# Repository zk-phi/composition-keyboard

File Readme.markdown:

# Composition 0.1

Choc V2 スイッチを採用した一体型・直交配列 40% キーボードです。 Choc V2 由来の薄さと、強めにつけた丸みが特徴的な可愛めのデザインになっています。透明アクリルで作るとよく光ります。

また自分のキーボードではお馴染みになっている、内部の空洞を廃した積層ケースを採用しており、アクリルにしてはしっかりした打鍵感を実現しています。今回はスイッチの性質上プレートレスの設計になっており、 PCB とケースの間の空間がまったくないので、他の作品よりもやや硬めの打鍵感になります。 PCB とケースの間にゴムワッシャなどの緩衝材を入れても問題なく使えることを確認しているので、柔らかい打鍵感が好きな場合はなんちゃってガスケットマウント化して使うのもアリかもしれないです。

# 注意

Choc V2 は「MX 互換スイッチと同じキーキャップをはめることができるが、 MX 互換スイッチよりかなり薄い」という特殊なスイッチです。

キーキャップの選択肢問題をクリアしつつキーボードを薄型化できる優秀なスイッチですが、いくつか注意点もあります。

## 全ての MX 互換キーキャップが使えるわけではない

キーキャップ側は Choc V2 を想定して設計されているわけではないので、一部噛み合わないものもあるようです。把握している範囲では、 GMK などの Cherry プロファイル、 RAMA の GRID キーキャップなどは難ありでした。

## トッププレートなし設計

トッププレートがキーキャップに干渉してしまうため、トッププレートなしの設計になっています。そのため、スイッチを半田付けする際の位置決めにコツが要ります。また基板を直接アクリル板に固定する都合、基板の歪みがキーボード全体の歪みに繋がりやすいです。

対策についても組み立てガイドの中で解説していますのでご確認ください。

## Pro Micro のレイアウトについて

このキーボードは Pro Micro を採用しつつ Choc V2 の薄さも活かすため、 Pro Micro 部分をケースの外に追い出す設計になっています（写真３枚目参照）。

無茶な使い方 (Pro Micro が外れかけた状態で金属製の机に置く、とか…) をするとショートの危険があるため、心配な方は

- あえてコンスルーを使わずに Pro Micro を直接半田付けして、ゆるまないようにする
- 絶縁テープ等をあらかじめ貼っておく

など各自工夫してお使いください（自分はあまり気にせず使っています）。

# 必要なもの

キット
- 基板
- トップフレーム 2mm x 1, 3mm x 1
- ミドルプレート (2mm)
- ボトムプレート上 (3mm)
- ボトムプレート下 (3mm)

おまけ
- ボトムプレート下 (2mm)

汎用部品
- キースイッチ, キーキャップ, ダイオード 1N4148w x41
- LED SK6812mini x56
- 2pin タクトスイッチ x1
- Pro Micro + ピンヘッダまたはコンスルー
- M2 ねじ 14mm x13, 6mm x7
- M2 ナット x20
- ゴムクッション x4 以上

カスタマイズに使えそうな部品 (任意)
- ゴムワッシャ

# 予備部品について

「ボトムプレート下」に 2mm のものを使ってさらに 1mm 薄くすることもできます。

打面を 1mm 下げ打鍵感を変化させられるほか、デザイン的にもミドルプレートを中心に上下対称となって綺麗に見えます。

ただし、 Pro Micro に取り付けたコンスルー（ピンヘッダ）の足がケースをはみ出してしまうため、足をカットするなどして、机に触れてしまうことがないようひと工夫する必要があります。

組み立てガイドではより無難な 3mm をデフォルトとしますが、興味のある方は自己責任にてチャンレンジしてみてください。

# 組み立て
## ProMicro の準備
### ProMicro にファームウェアを書き込んでおく

ProMicro にあらかじめファームウェアを書き込んでおきます。

https://github.com/zk-phi/keyboard-buildguide-common/blob/master/firmware.markdown

[こちら](https://github.com/zk-phi/qmk_firmware) に私の使っているキーマップがアップロードされています。

```terminal
make composition:phi:avrdude
```

### ProMicro にコンスルーを実装しておく

ProMicro を基板に連結するためのコンスルーを実装します。

https://github.com/zk-phi/keyboard-buildguide-common/blob/master/conthrough.markdown

このキーボードでは ProMicro を「部品面が内側になるように」使用します。

## 基板の歪みを矯正

このキーボードは基板を直接ケースにねじ止めして一体化させる設計になっているので、基板の歪みが激しいと、最終的に完成するキーボード全体も歪んでしまうことがあります。

そこで、半田付けを始める前に、基板を損傷しない程度に軽く歪みを矯正しておくことをおすすめします。

## 基板に各パーツを実装

### ダイオードを実装

ダイオードを実装します。

https://github.com/zk-phi/keyboard-buildguide-common/blob/master/diode.markdown

表面実装部品は、ガイドの印から大きくはみ出して取り付けてしまうと「ボトムプレート上」と干渉してケースが組めなくなってしまいますので、なるべく丁寧に位置を合わせてください。

### LED を実装 (オプション)

LED を実装します。

https://github.com/zk-phi/keyboard-buildguide-common/blob/master/neopixel.markdown

LED の実装順は Pro Micro 側上段のバックライト (背面実装・赤) からスタートして Z 字に降りていき、下段まで行ったらアンダーグロー (表面実装・青) で折り返すように進みます。

### スイッチを実装

最後にスイッチを実装します。

https://github.com/zk-phi/keyboard-buildguide-common/blob/master/switch.markdown

### Pro Micro の仕上げ

Pro Micro がゆるんでしまうのが不安な方は、 Pro Micro を基板に半田付けします。

## 基板とボトムプレート上を合体

「ボトムプレート上」と基板を短い方のネジで連結します。

基板とボトムプレートの間にゴムワッシャなどの緩衝材を挟んで、なんちゃってガスケットマウントのようにするのもアリだと思います（問題なく使えました）。

## ケースを組み立て

下から

- ボトムプレート下
- 基板＋ボトムプレート上
- ミドルフレーム
- トップフレーム (3mm)
- トップフレーム (2mm)

の順に重ね、長い方のネジで連結します。

キーキャップをはめて、ゴムクッションを貼り付ければ完成です。ゴムクッションを増やした方が剛性感が得られますが、ケースにたわみが出た時にガタつきを起こしてしまいます。このキーボードは薄く、また基板がケースと一体になっておりたわみやすいので、私は四隅だけにつけて使用しています。

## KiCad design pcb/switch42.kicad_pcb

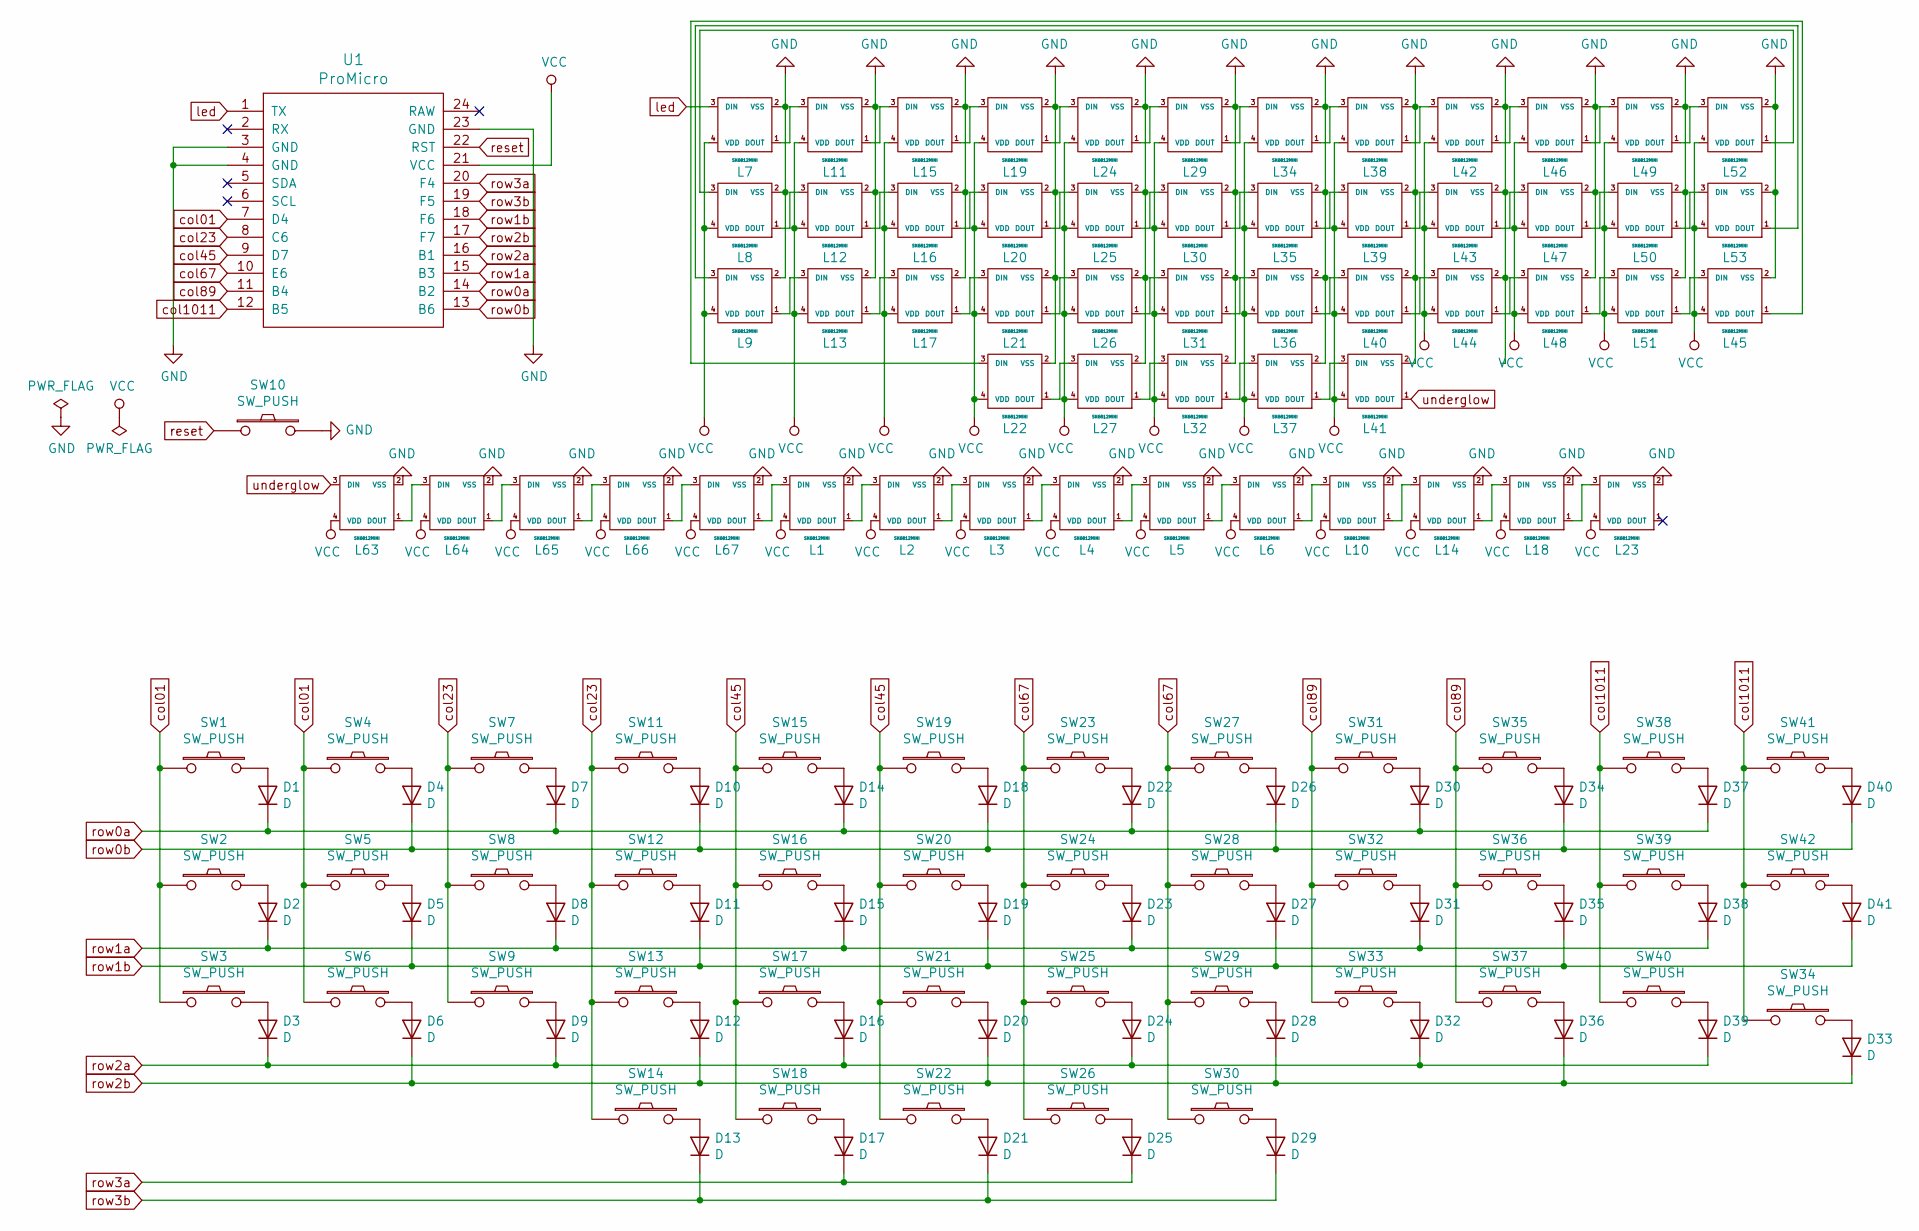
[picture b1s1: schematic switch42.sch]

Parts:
D1, D2, D3, D4, D5, D6, D7, D8, D9, D10, D11, D12, D13, D14, D15, D16, D17, D18, D19, D20, D21, D22, D23, D24, D25, D26, D27, D28, D29, D30, D31, D32, D33, D34, D35, D36, D37, D38, D39, D40, D41: D; D_SMD-irreversible
L1, L2, L3, L4, L5, L6, L10, L14, L18, L23, L63, L64, L65, L66, L67: SK6812MINI; SK6812MINI-underglow-irreversible
L7, L8, L9, L11, L12, L13, L15, L16, L17, L19, L20, L21, L22, L24, L25, L26, L27, L29, L30, L31, L32, L34, L35, L36, L37, L38, L39, L40, L41, L42, L43, L44, L45, L46, L47, L48, L49, L50, L51, L52, L53: SK6812MINI; SK6812MINI_narrow-irreversible
SW1, SW2, SW3, SW4, SW5, SW6, SW7, SW8, SW9, SW11, SW12, SW13, SW14, SW15, SW16, SW17, SW18, SW19, SW20, SW21, SW22, SW23, SW24, SW25, SW26, SW27, SW28, SW29, SW30, SW31, SW32, SW33, SW34, SW35, SW36, SW37, SW38, SW39, SW40, SW41, SW42: SW_PUSH; ChocV2_1.00u-irreversible
SW10: SW_PUSH; ResetSW-irreversible
U1: ProMicro; ProMicro_Reversed_Conthrough-irreversible

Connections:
GND: L1.2 (VSS), L2.2 (VSS), L3.2 (VSS), L4.2 (VSS), L5.2 (VSS), L6.2 (VSS), L7.2 (VSS), L8.2 (VSS), L9.2 (VSS), L10.2 (VSS), L11.2 (VSS), L12.2 (VSS), L13.2 (VSS), L14.2 (VSS), L15.2 (VSS), L16.2 (VSS), L17.2 (VSS), L18.2 (VSS), L19.2 (VSS), L20.2 (VSS), L21.2 (VSS), L22.2 (VSS), L23.2 (VSS), L24.2 (VSS), L25.2 (VSS), L26.2 (VSS), L27.2 (VSS), L29.2 (VSS), L30.2 (VSS), L31.2 (VSS), L32.2 (VSS), L34.2 (VSS), L35.2 (VSS), L36.2 (VSS), L37.2 (VSS), L38.2 (VSS), L39.2 (VSS), L40.2 (VSS), L41.2 (VSS), L42.2 (VSS), L43.2 (VSS), L44.2 (VSS), L45.2 (VSS), L46.2 (VSS), L47.2 (VSS), L48.2 (VSS), L49.2 (VSS), L50.2 (VSS), L51.2 (VSS), L52.2 (VSS), L53.2 (VSS), L63.2 (VSS), L64.2 (VSS), L65.2 (VSS), L66.2 (VSS), L67.2 (VSS), SW10.2, U1.3 (GND), U1.4 (GND), U1.23 (GND)
unnamed: D1.2 (A), SW1.2
unnamed: D2.2 (A), SW2.2
unnamed: D3.2 (A), SW3.2
unnamed: D4.2 (A), SW4.2
unnamed: D5.2 (A), SW5.2
unnamed: D6.2 (A), SW6.2
unnamed: D7.2 (A), SW7.2
unnamed: D8.2 (A), SW8.2
unnamed: D9.2 (A), SW9.2
unnamed: D10.2 (A), SW11.2
unnamed: D11.2 (A), SW12.2
unnamed: D12.2 (A), SW13.2
unnamed: D13.2 (A), SW14.2
unnamed: D14.2 (A), SW15.2
unnamed: D15.2 (A), SW16.2
unnamed: D16.2 (A), SW17.2
unnamed: D17.2 (A), SW18.2
unnamed: D18.2 (A), SW19.2
unnamed: D19.2 (A), SW20.2
unnamed: D20.2 (A), SW21.2
unnamed: D21.2 (A), SW22.2
unnamed: D22.2 (A), SW23.2
unnamed: D23.2 (A), SW24.2
unnamed: D24.2 (A), SW25.2
unnamed: D25.2 (A), SW26.2
unnamed: D26.2 (A), SW27.2
unnamed: D27.2 (A), SW28.2
unnamed: D28.2 (A), SW29.2
unnamed: D29.2 (A), SW30.2
unnamed: D30.2 (A), SW31.2
unnamed: D31.2 (A), SW32.2
unnamed: D32.2 (A), SW33.2
unnamed: D33.2 (A), SW34.2
unnamed: D34.2 (A), SW35.2
unnamed: D35.2 (A), SW36.2
unnamed: D36.2 (A), SW37.2
unnamed: D37.2 (A), SW38.2
unnamed: D38.2 (A), SW39.2
unnamed: D39.2 (A), SW40.2
unnamed: D40.2 (A), SW41.2
unnamed: D41.2 (A), SW42.2
unnamed: L1.1 (DOUT), L2.3 (DIN)
unnamed: L1.3 (DIN), L67.1 (DOUT)
unnamed: L2.1 (DOUT), L3.3 (DIN)
unnamed: L3.1 (DOUT), L4.3 (DIN)
unnamed: L4.1 (DOUT), L5.3 (DIN)
unnamed: L5.1 (DOUT), L6.3 (DIN)
unnamed: L10.1 (DOUT), L14.3 (DIN)
unnamed: L6.1 (DOUT), L10.3 (DIN)
unnamed: L11.1 (DOUT), L15.3 (DIN)
unnamed: L7.1 (DOUT), L11.3 (DIN)
unnamed: L12.1 (DOUT), L16.3 (DIN)
unnamed: L8.1 (DOUT), L12.3 (DIN)
unnamed: L13.1 (DOUT), L17.3 (DIN)
unnamed: L9.1 (DOUT), L13.3 (DIN)
unnamed: L14.1 (DOUT), L18.3 (DIN)
unnamed: L15.1 (DOUT), L19.3 (DIN)
unnamed: L16.1 (DOUT), L20.3 (DIN)
unnamed: L17.1 (DOUT), L21.3 (DIN)
unnamed: L18.1 (DOUT), L23.3 (DIN)
unnamed: L19.1 (DOUT), L24.3 (DIN)
unnamed: L20.1 (DOUT), L25.3 (DIN)
unnamed: L21.1 (DOUT), L26.3 (DIN)
unnamed: L22.1 (DOUT), L27.3 (DIN)
unnamed: L22.3 (DIN), L45.1 (DOUT)
unnamed: L24.1 (DOUT), L29.3 (DIN)
unnamed: L25.1 (DOUT), L30.3 (DIN)
unnamed: L26.1 (DOUT), L31.3 (DIN)
unnamed: L27.1 (DOUT), L32.3 (DIN)
unnamed: L29.1 (DOUT), L34.3 (DIN)
unnamed: L30.1 (DOUT), L35.3 (DIN)
unnamed: L31.1 (DOUT), L36.3 (DIN)
unnamed: L32.1 (DOUT), L37.3 (DIN)
unnamed: L34.1 (DOUT), L38.3 (DIN)
unnamed: L35.1 (DOUT), L39.3 (DIN)
unnamed: L36.1 (DOUT), L40.3 (DIN)
unnamed: L37.1 (DOUT), L41.3 (DIN)
unnamed: L38.1 (DOUT), L42.3 (DIN)
unnamed: L39.1 (DOUT), L43.3 (DIN)
unnamed: L40.1 (DOUT), L44.3 (DIN)
unnamed: L42.1 (DOUT), L46.3 (DIN)
unnamed: L43.1 (DOUT), L47.3 (DIN)
unnamed: L44.1 (DOUT), L48.3 (DIN)
unnamed: L45.3 (DIN), L51.1 (DOUT)
unnamed: L46.1 (DOUT), L49.3 (DIN)
unnamed: L47.1 (DOUT), L50.3 (DIN)
unnamed: L48.1 (DOUT), L51.3 (DIN)
unnamed: L49.1 (DOUT), L52.3 (DIN)
unnamed: L50.1 (DOUT), L53.3 (DIN)
unnamed: L8.3 (DIN), L52.1 (DOUT)
unnamed: L9.3 (DIN), L53.1 (DOUT)
unnamed: L63.1 (DOUT), L64.3 (DIN)
unnamed: L64.1 (DOUT), L65.3 (DIN)
unnamed: L65.1 (DOUT), L66.3 (DIN)
unnamed: L66.1 (DOUT), L67.3 (DIN)
VCC: L1.4 (VDD), L2.4 (VDD), L3.4 (VDD), L4.4 (VDD), L5.4 (VDD), L6.4 (VDD), L7.4 (VDD), L8.4 (VDD), L9.4 (VDD), L10.4 (VDD), L11.4 (VDD), L12.4 (VDD), L13.4 (VDD), L14.4 (VDD), L15.4 (VDD), L16.4 (VDD), L17.4 (VDD), L18.4 (VDD), L19.4 (VDD), L20.4 (VDD), L21.4 (VDD), L22.4 (VDD), L23.4 (VDD), L24.4 (VDD), L25.4 (VDD), L26.4 (VDD), L27.4 (VDD), L29.4 (VDD), L30.4 (VDD), L31.4 (VDD), L32.4 (VDD), L34.4 (VDD), L35.4 (VDD), L36.4 (VDD), L37.4 (VDD), L38.4 (VDD), L39.4 (VDD), L40.4 (VDD), L41.4 (VDD), L42.4 (VDD), L43.4 (VDD), L44.4 (VDD), L45.4 (VDD), L46.4 (VDD), L47.4 (VDD), L48.4 (VDD), L49.4 (VDD), L50.4 (VDD), L51.4 (VDD), L52.4 (VDD), L53.4 (VDD), L63.4 (VDD), L64.4 (VDD), L65.4 (VDD), L66.4 (VDD), L67.4 (VDD), U1.21 (VCC)
col01: SW1.1, SW2.1, SW3.1, SW4.1, SW5.1, SW6.1, U1.7 (D4)
col23: SW7.1, SW8.1, SW9.1, SW11.1, SW12.1, SW13.1, SW14.1, U1.8 (C6)
col45: SW15.1, SW16.1, SW17.1, SW18.1, SW19.1, SW20.1, SW21.1, SW22.1, U1.9 (D7)
col67: SW23.1, SW24.1, SW25.1, SW26.1, SW27.1, SW28.1, SW29.1, SW30.1, U1.10 (E6)
col89: SW31.1, SW32.1, SW33.1, SW35.1, SW36.1, SW37.1, U1.11 (B4)
col1011: SW34.1, SW38.1, SW39.1, SW40.1, SW41.1, SW42.1, U1.12 (B5)
led: L7.3 (DIN), U1.1 (TX)
reset: SW10.1, U1.22 (RST)
row0a: D1.1 (K), D7.1 (K), D14.1 (K), D22.1 (K), D30.1 (K), D37.1 (K), U1.14 (B2)
row0b: D4.1 (K), D10.1 (K), D18.1 (K), D26.1 (K), D34.1 (K), D40.1 (K), U1.13 (B6)
row1a: D2.1 (K), D8.1 (K), D15.1 (K), D23.1 (K), D31.1 (K), D38.1 (K), U1.15 (B3)
row1b: D5.1 (K), D11.1 (K), D19.1 (K), D27.1 (K), D35.1 (K), D41.1 (K), U1.18 (F6)
row2a: D3.1 (K), D9.1 (K), D16.1 (K), D24.1 (K), D32.1 (K), D39.1 (K), U1.16 (B1)
row2b: D6.1 (K), D12.1 (K), D20.1 (K), D28.1 (K), D33.1 (K), D36.1 (K), U1.17 (F7)
row3a: D17.1 (K), D25.1 (K), U1.20 (F4)
row3b: D13.1 (K), D21.1 (K), D29.1 (K), U1.19 (F5)
underglow: L41.1 (DOUT), L63.3 (DIN)

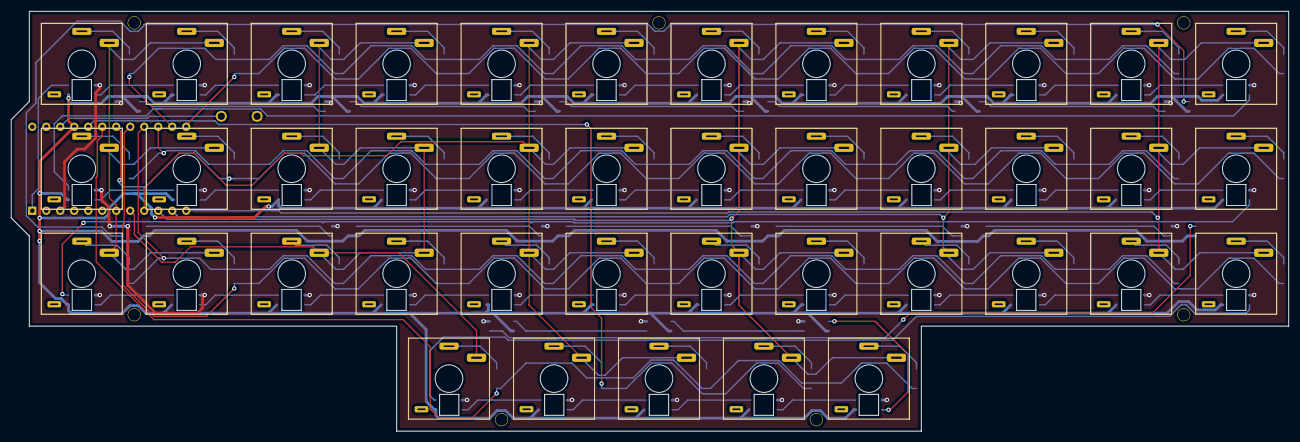
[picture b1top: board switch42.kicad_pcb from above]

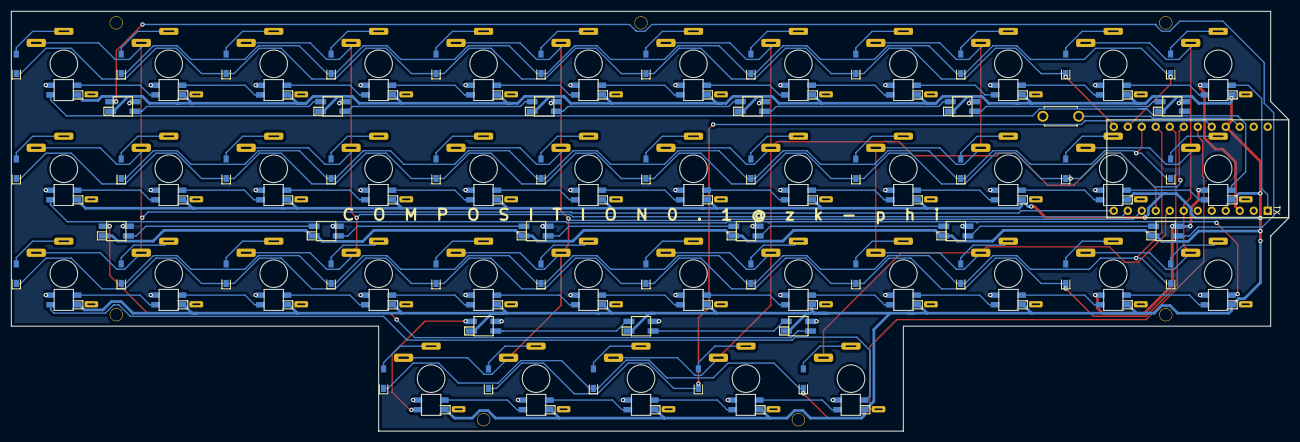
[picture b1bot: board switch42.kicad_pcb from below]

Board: 2 copper layers, 231.9 x 76.2 mm, 147 parts (58 on the bottom side), 114 nets.

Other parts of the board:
Ref**: Val**; M2_SCREW_HOLE_Plated
Ref**#2, Ref**#3, Ref**#4, Ref**#5, Ref**#6, Ref**#7: Val**; M2_SCREW_HOLE_Plated

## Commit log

2020-07-27 Add Readme
2020-08-20 Fix typo
2020-08-23 Fix Readme
2020-08-25 Add pcb
2020-08-25 Add LICENSE
2020-08-30 Add link title
2020-08-30 Heading
